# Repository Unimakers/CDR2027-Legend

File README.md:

# CDR 2027 - Legend

Dépôt de l'équipe **Unimakers** (MakerSpace Amiens) pour la **Coupe de France de Robotique 2027**, thème « The Legend of Camelot ».

Nous préparons un **robot principal** et des **PAMI** (petits robots autonomes qui partent de l'écurie en fin de match).

- **Documentation : [unimakers.fr/CDR2027-Legend](https://unimakers.fr/CDR2027-Legend/)** (objectifs, robots, journaux de bord)
- **CAO : [projet Onshape](https://cad.onshape.com/documents/a1dd7e986cf35e5710cc0af1/v/c28c25944dc0cfd69f9db5c7/e/192be7f926e66b5b2fba6ecb)**

## Contenu du dépôt

| Dossier | Contenu |
|:--|:--|
| [`fw/`](fw/) | Firmware des PAMI : ESP32-S3 (PlatformIO, Arduino) et coprocesseur Luckfox (Python) |
| [`ecad/`](ecad/) | Cartes électroniques KiCad : PAMI V1 (en service), PAMI V2 (en conception), robot principal |
| [`mcad/`](mcad/) | Exports de pièces (STL) ; la CAO elle-même est sur Onshape |
| [`docs/`](docs/) | Site de documentation (Jekyll, thème Just the Docs), publié sur GitHub Pages |

## Avancement

- **PAMI** : carte V1 câblée et firmware fonctionnel (odométrie, stratégies en JSON, interface web, mise à jour sans fil). Carte V2 routée, pas encore fabriquée.
- **Robot principal** : carte électronique en cours sous KiCad, module encodeur testé, prototype de l'actionneur de levage des murs. Pas encore de code.

Le détail, semaine par semaine, est dans les [journaux de bord](https://unimakers.fr/CDR2027-Legend/journaux/).

## Démarrer

```sh
# Firmware PAMI (carte V1)
cd fw/fw-pami-carte-v1
pio run

# Site de documentation en local
cd docs
bundle install
bundle exec jekyll serve
```

## Contribuer

Les commits suivent le format `[TAG] Message`, avec les tags `[FW]`, `[DOC]`, `[ECAD]` et `[GLOBAL]`.

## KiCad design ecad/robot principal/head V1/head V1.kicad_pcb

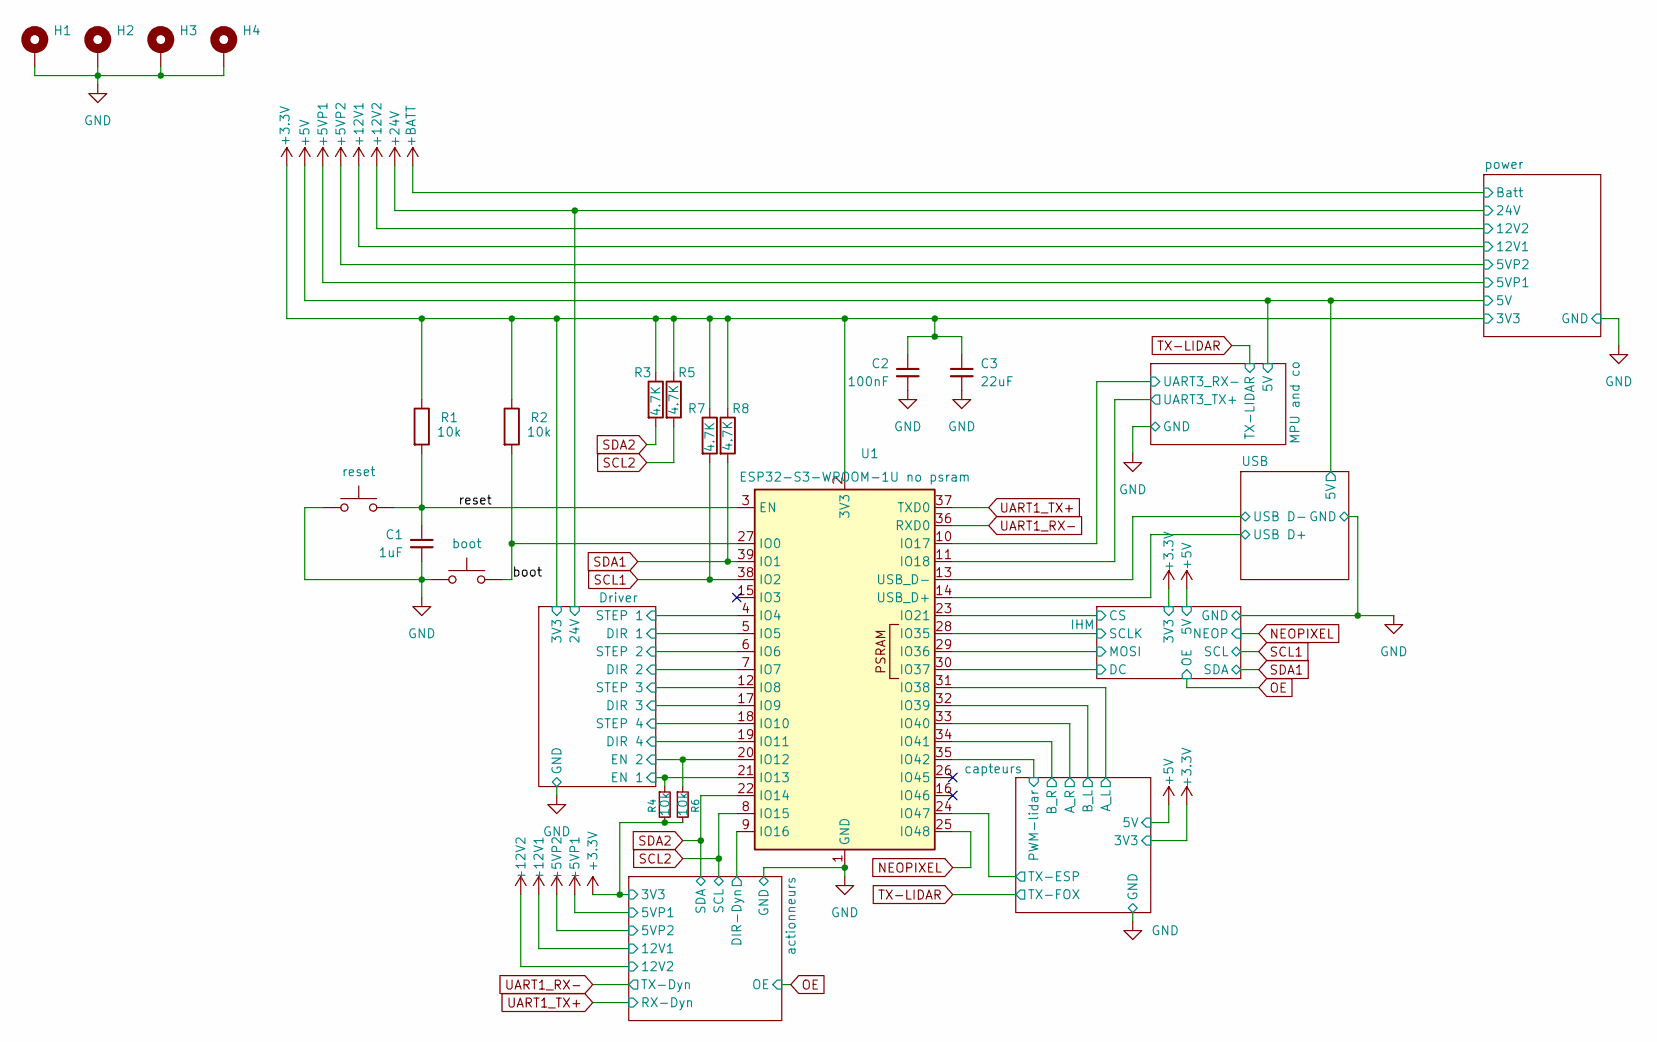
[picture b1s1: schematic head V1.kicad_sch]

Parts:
C1: 1uF; C_0805_2012Metric_Pad1.18x1.45mm_HandSolder
C2: 100nF; C_0805_2012Metric_Pad1.18x1.45mm_HandSolder
C3: 22uF; C_0805_2012Metric_Pad1.18x1.45mm_HandSolder
H1, H2, H3, H4: MountingHole_Pad; MountingHole_3.2mm_M3_Pad_Via
R1, R2, R4, R6: 10k; R_0805_2012Metric_Pad1.20x1.40mm_HandSolder
R3, R5, R7, R8: 4.7K; R_0805_2012Metric_Pad1.20x1.40mm_HandSolder
SW1: reset; SW_Push_SPST_NO_Alps_SKRK
SW2: boot; SW_Push_SPST_NO_Alps_SKRK
U1: ESP32-S3-WROOM-1U no psram; ESP32-S3-WROOM-1U

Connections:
+3.3V: C2.1, C3.1, R1.1, R2.1, R3.1, R4.2, R5.1, R6.2, R7.1, R8.1, U1.2 (3V3); also elsewhere on the board
/Driver/DIR 1: U1.5 (IO5); also elsewhere on the board
/Driver/DIR 2: U1.7 (IO7); also elsewhere on the board
/Driver/DIR 3: U1.17 (IO9); also elsewhere on the board
/Driver/DIR 4: U1.19 (IO11); also elsewhere on the board
/Driver/EN 1: R4.1, U1.21 (IO13); also elsewhere on the board
/Driver/EN 2: R6.1, U1.20 (IO12); also elsewhere on the board
/Driver/STEP 1: U1.4 (IO4); also elsewhere on the board
/Driver/STEP 2: U1.6 (IO6); also elsewhere on the board
/Driver/STEP 3: U1.12 (IO8); also elsewhere on the board
/Driver/STEP 4: U1.18 (IO10); also elsewhere on the board
/IHM/CS: U1.23 (IO21); also elsewhere on the board
/IHM/DC: U1.30 (IO37); also elsewhere on the board
/IHM/MOSI: U1.29 (IO36); also elsewhere on the board
/IHM/SCLK: U1.28 (IO35); also elsewhere on the board
/MPU and co/UART3_RX-: U1.10 (IO17); also elsewhere on the board
/MPU and co/UART3_TX+: U1.11 (IO18); also elsewhere on the board
/USB/USB D+: U1.14 (USB_D+); also elsewhere on the board
/USB/USB D-: U1.13 (USB_D-); also elsewhere on the board
/actionneurs/DIR-Dyn: U1.9 (IO16); also elsewhere on the board
/boot: R2.2, SW2.2, U1.27 (IO0)
/capteurs/A_L: U1.31 (IO38); also elsewhere on the board
/capteurs/A_R: U1.33 (IO40); also elsewhere on the board
/capteurs/B_L: U1.32 (IO39); also elsewhere on the board
/capteurs/B_R: U1.34 (IO41); also elsewhere on the board
/capteurs/PWM-lidar: U1.35 (IO42); also elsewhere on the board
/capteurs/TX-ESP: U1.24 (IO47); also elsewhere on the board
/reset: C1.1, R1.2, SW1.2, U1.3 (EN)
GND: C1.2, C2.2, C3.2, H1.1 (1_1), H2.1 (1_1), H3.1 (1_1), H4.1 (1_1), SW1.1, SW2.1, U1.1 (GND), U1.40 (GND), U1.41 (GND); also elsewhere on the board
NEOPIXEL: U1.25 (IO48); also elsewhere on the board
SCL1: R7.2, U1.38 (IO2); also elsewhere on the board
SCL2: R5.2, U1.8 (IO15); also elsewhere on the board
SDA1: R8.2, U1.39 (IO1); also elsewhere on the board
SDA2: R3.2, U1.22 (IO14); also elsewhere on the board
UART1_RX-: U1.36 (RXD0); also elsewhere on the board
UART1_TX+: U1.37 (TXD0); also elsewhere on the board

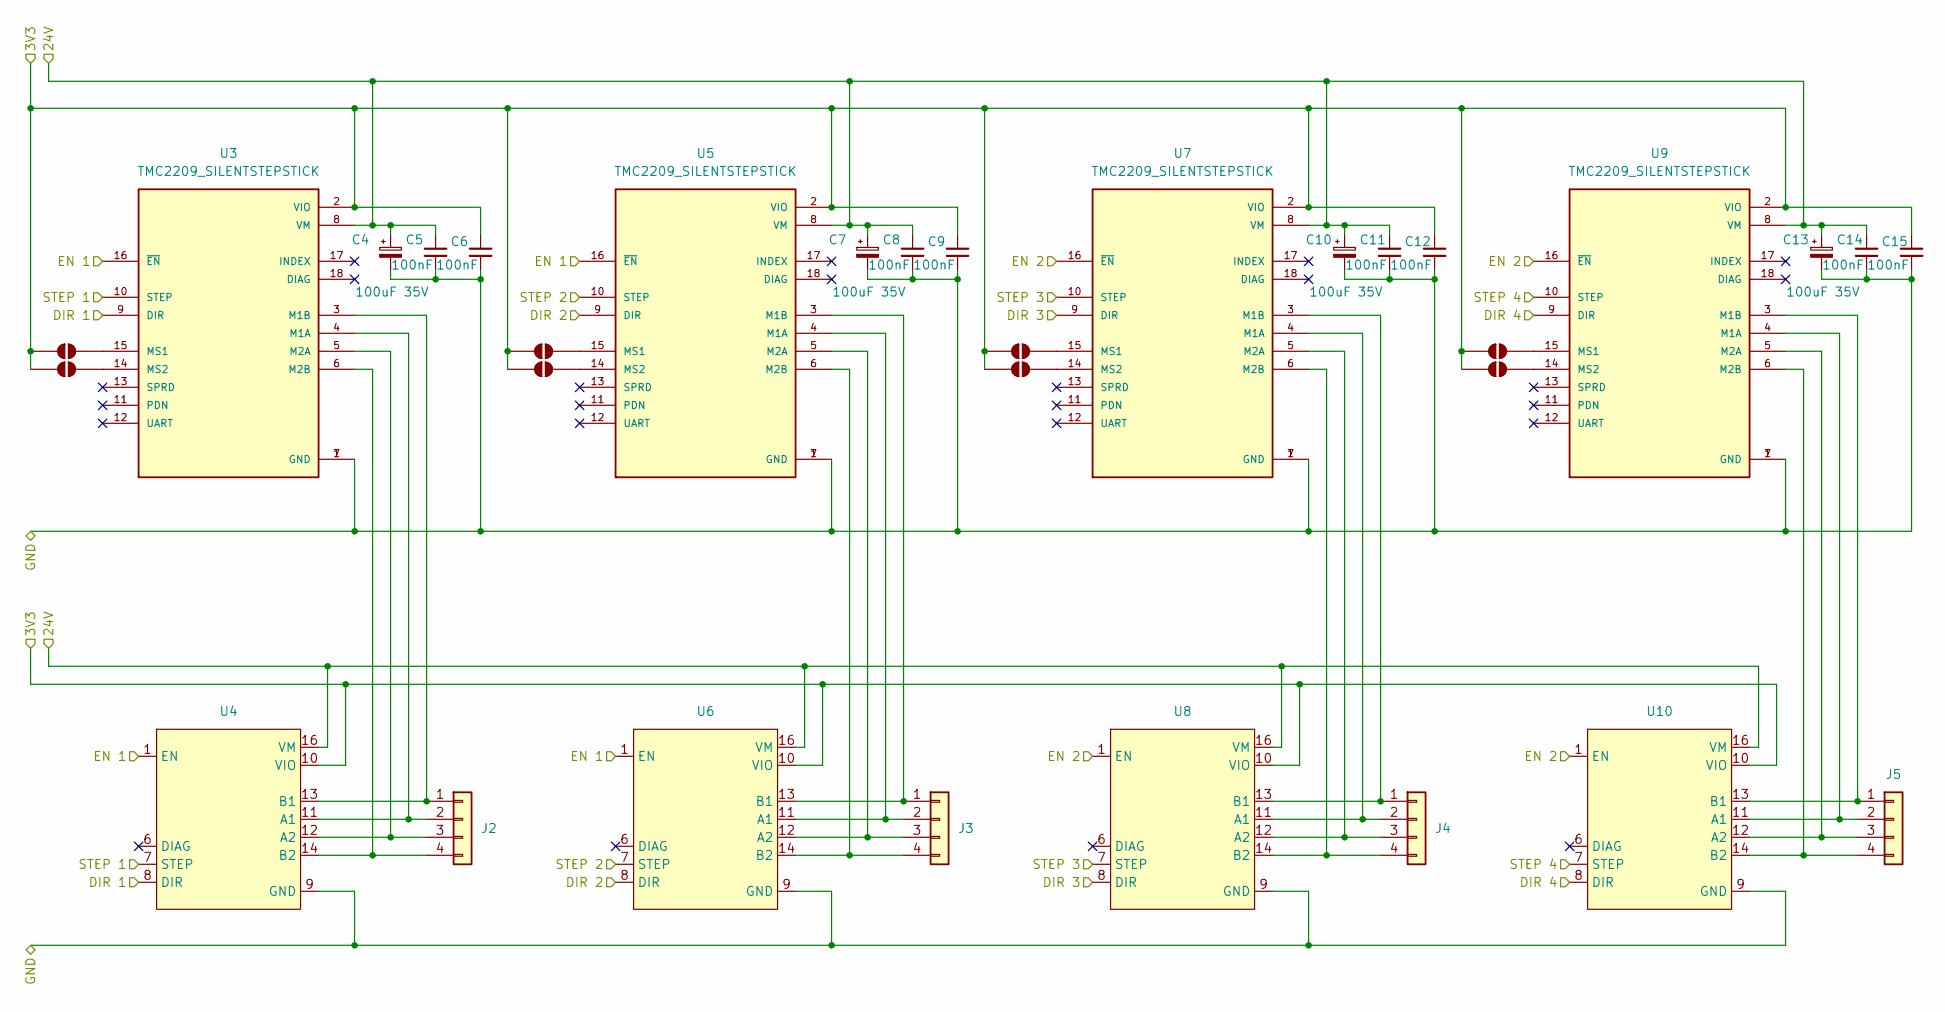
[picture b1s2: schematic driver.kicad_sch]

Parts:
C4, C7, C10, C13: 100uF 35V; CP_Radial_D6.3mm_P2.50mm
C5, C6, C8, C9, C11, C12, C14, C15: 100nF; C_0805_2012Metric_Pad1.18x1.45mm_HandSolder
J2, J3, J4, J5: Conn_01x04; Molex_KK-254_AE-6410-04A_1x04_P2.54mm_Vertical
JP1, JP2, JP3, JP4, JP5, JP6, JP7, JP8: SolderJumper_2_Open; SolderJumper-2_P1.3mm_Open_RoundedPad1.0x1.5mm
U3, U5, U7, U9: TMC2209_SILENTSTEPSTICK; MODULE_TMC2209_SILENTSTEPSTICK; PARTREV 1.20
U4, U6, U8, U10: ez 2209

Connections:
+3.3V: C6.1, C9.1, C12.1, C15.1, JP1.1 (A), JP2.1 (A), JP3.1 (A), JP4.1 (A), JP5.1 (A), JP6.1 (A), JP7.1 (A), JP8.1 (A), U3.2 (VIO), U4.10 (VIO), U5.2 (VIO), U6.10 (VIO), U7.2 (VIO), U8.10 (VIO), U9.2 (VIO), U10.10 (VIO); also elsewhere on the board
+24V: C4.1, C5.1, C7.1, C8.1, C10.1, C11.1, C13.1, C14.1, U3.8 (VM), U4.16 (VM), U5.8 (VM), U6.16 (VM), U7.8 (VM), U8.16 (VM), U9.8 (VM), U10.16 (VM); also elsewhere on the board
/Driver/DIR 1: U3.9 (DIR), U4.8 (DIR); also elsewhere on the board
/Driver/DIR 2: U5.9 (DIR), U6.8 (DIR); also elsewhere on the board
/Driver/DIR 3: U7.9 (DIR), U8.8 (DIR); also elsewhere on the board
/Driver/DIR 4: U9.9 (DIR), U10.8 (DIR); also elsewhere on the board
/Driver/EN 1: U3.16 (~EN), U4.1 (EN), U5.16 (~EN), U6.1 (EN); also elsewhere on the board
/Driver/EN 2: U7.16 (~EN), U8.1 (EN), U9.16 (~EN), U10.1 (EN); also elsewhere on the board
/Driver/STEP 1: U3.10 (STEP), U4.7 (STEP); also elsewhere on the board
/Driver/STEP 2: U5.10 (STEP), U6.7 (STEP); also elsewhere on the board
/Driver/STEP 3: U7.10 (STEP), U8.7 (STEP); also elsewhere on the board
/Driver/STEP 4: U9.10 (STEP), U10.7 (STEP); also elsewhere on the board
GND: C4.2, C5.2, C6.2, C7.2, C8.2, C9.2, C10.2, C11.2, C12.2, C13.2, C14.2, C15.2, U3.1 (GND), U3.7 (GND), U4.9 (GND), U4.15 (GND), U5.1 (GND), U5.7 (GND), U6.9 (GND), U6.15 (GND), U7.1 (GND), U7.7 (GND), U8.9 (GND), U8.15 (GND), U9.1 (GND), U9.7 (GND), U10.9 (GND), U10.15 (GND); also elsewhere on the board
unnamed: J2.1, U3.3 (M1B), U4.13 (B1)
unnamed: J2.2, U3.4 (M1A), U4.11 (A1)
unnamed: J2.3, U3.5 (M2A), U4.12 (A2)
unnamed: J2.4, U3.6 (M2B), U4.14 (B2)
unnamed: J3.1, U5.3 (M1B), U6.13 (B1)
unnamed: J3.2, U5.4 (M1A), U6.11 (A1)
unnamed: J3.3, U5.5 (M2A), U6.12 (A2)
unnamed: J3.4, U5.6 (M2B), U6.14 (B2)
unnamed: J4.1, U7.3 (M1B), U8.13 (B1)
unnamed: J4.2, U7.4 (M1A), U8.11 (A1)
unnamed: J4.3, U7.5 (M2A), U8.12 (A2)
unnamed: J4.4, U7.6 (M2B), U8.14 (B2)
unnamed: J5.1, U9.3 (M1B), U10.13 (B1)
unnamed: J5.2, U9.4 (M1A), U10.11 (A1)
unnamed: J5.3, U9.5 (M2A), U10.12 (A2)
unnamed: J5.4, U9.6 (M2B), U10.14 (B2)
unnamed: JP1.2 (B), U3.15 (MS1)
unnamed: JP2.2 (B), U3.14 (MS2)
unnamed: JP3.2 (B), U5.15 (MS1)
unnamed: JP4.2 (B), U5.14 (MS2)
unnamed: JP5.2 (B), U7.15 (MS1)
unnamed: JP6.2 (B), U7.14 (MS2)
unnamed: JP7.2 (B), U9.15 (MS1)
unnamed: JP8.2 (B), U9.14 (MS2)

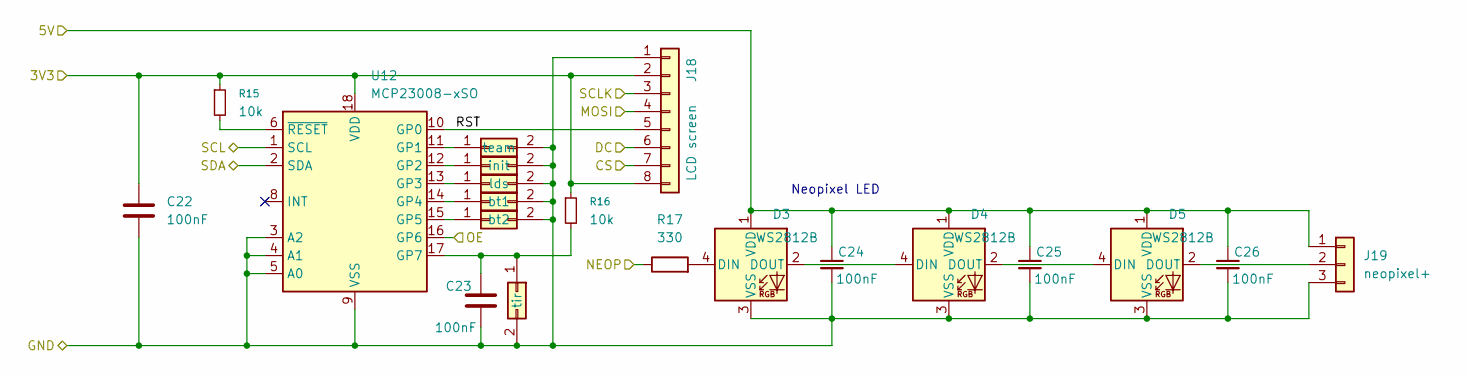
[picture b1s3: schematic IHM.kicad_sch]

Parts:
C22, C23, C24, C25, C26: 100nF; C_0805_2012Metric_Pad1.18x1.45mm_HandSolder
D3, D4, D5: WS2812B; LED_WS2812B_PLCC4_5.0x5.0mm_P3.2mm
J12: team; Molex_KK-254_AE-6410-02A_1x02_P2.54mm_Vertical
J13: init; Molex_KK-254_AE-6410-02A_1x02_P2.54mm_Vertical
J14: lds; Molex_KK-254_AE-6410-02A_1x02_P2.54mm_Vertical
J15: bt1; Molex_KK-254_AE-6410-02A_1x02_P2.54mm_Vertical
J16: bt2; Molex_KK-254_AE-6410-02A_1x02_P2.54mm_Vertical
J17: tir; Molex_KK-254_AE-6410-02A_1x02_P2.54mm_Vertical
J18: LCD screen; PinSocket_1x08_P2.54mm_Vertical
J19: neopixel+; Molex_KK-254_AE-6410-03A_1x03_P2.54mm_Vertical
R15, R16: 10k; R_0805_2012Metric_Pad1.20x1.40mm_HandSolder
R17: 330; R_0805_2012Metric_Pad1.20x1.40mm_HandSolder
U12: MCP23008-xSO; SOIC-18W_7.5x11.6mm_P1.27mm

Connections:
+3.3V: C22.1, J18.2, J18.8, R15.1, R16.1, U12.18 (VDD); also elsewhere on the board
+5V: C24.1, C25.1, C26.1, D3.1 (VDD), D4.1 (VDD), D5.1 (VDD), J19.1; also elsewhere on the board
/IHM/CS: J18.7; also elsewhere on the board
/IHM/DC: J18.6; also elsewhere on the board
/IHM/MOSI: J18.4; also elsewhere on the board
/IHM/RST: J18.5, U12.10 (GP0)
/IHM/SCLK: J18.3; also elsewhere on the board
GND: C22.2, C23.2, C24.2, C25.2, C26.2, D3.3 (VSS), D4.3 (VSS), D5.3 (VSS), J12.2, J13.2, J14.2, J15.2, J16.2, J17.2, J18.1, J19.3, U12.3 (A2), U12.4 (A1), U12.5 (A0), U12.9 (VSS); also elsewhere on the board
NEOPIXEL: R17.1; also elsewhere on the board
unnamed: D3.4 (DIN), R17.2
unnamed: D3.2 (DOUT), D4.4 (DIN)
unnamed: D4.2 (DOUT), D5.4 (DIN)
unnamed: D5.2 (DOUT), J19.2
unnamed: J12.1, U12.11 (GP1)
unnamed: J13.1, U12.12 (GP2)
unnamed: J14.1, U12.13 (GP3)
unnamed: J15.1, U12.14 (GP4)
unnamed: J16.1, U12.15 (GP5)
unnamed: C23.1, J17.1, R16.2, U12.17 (GP7)
unnamed: R15.2, U12.6 (~RESET)
OE: U12.16 (GP6); also elsewhere on the board
SCL1: U12.1 (SCL); also elsewhere on the board
SDA1: U12.2 (SDA); also elsewhere on the board

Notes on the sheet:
Neopixel LED

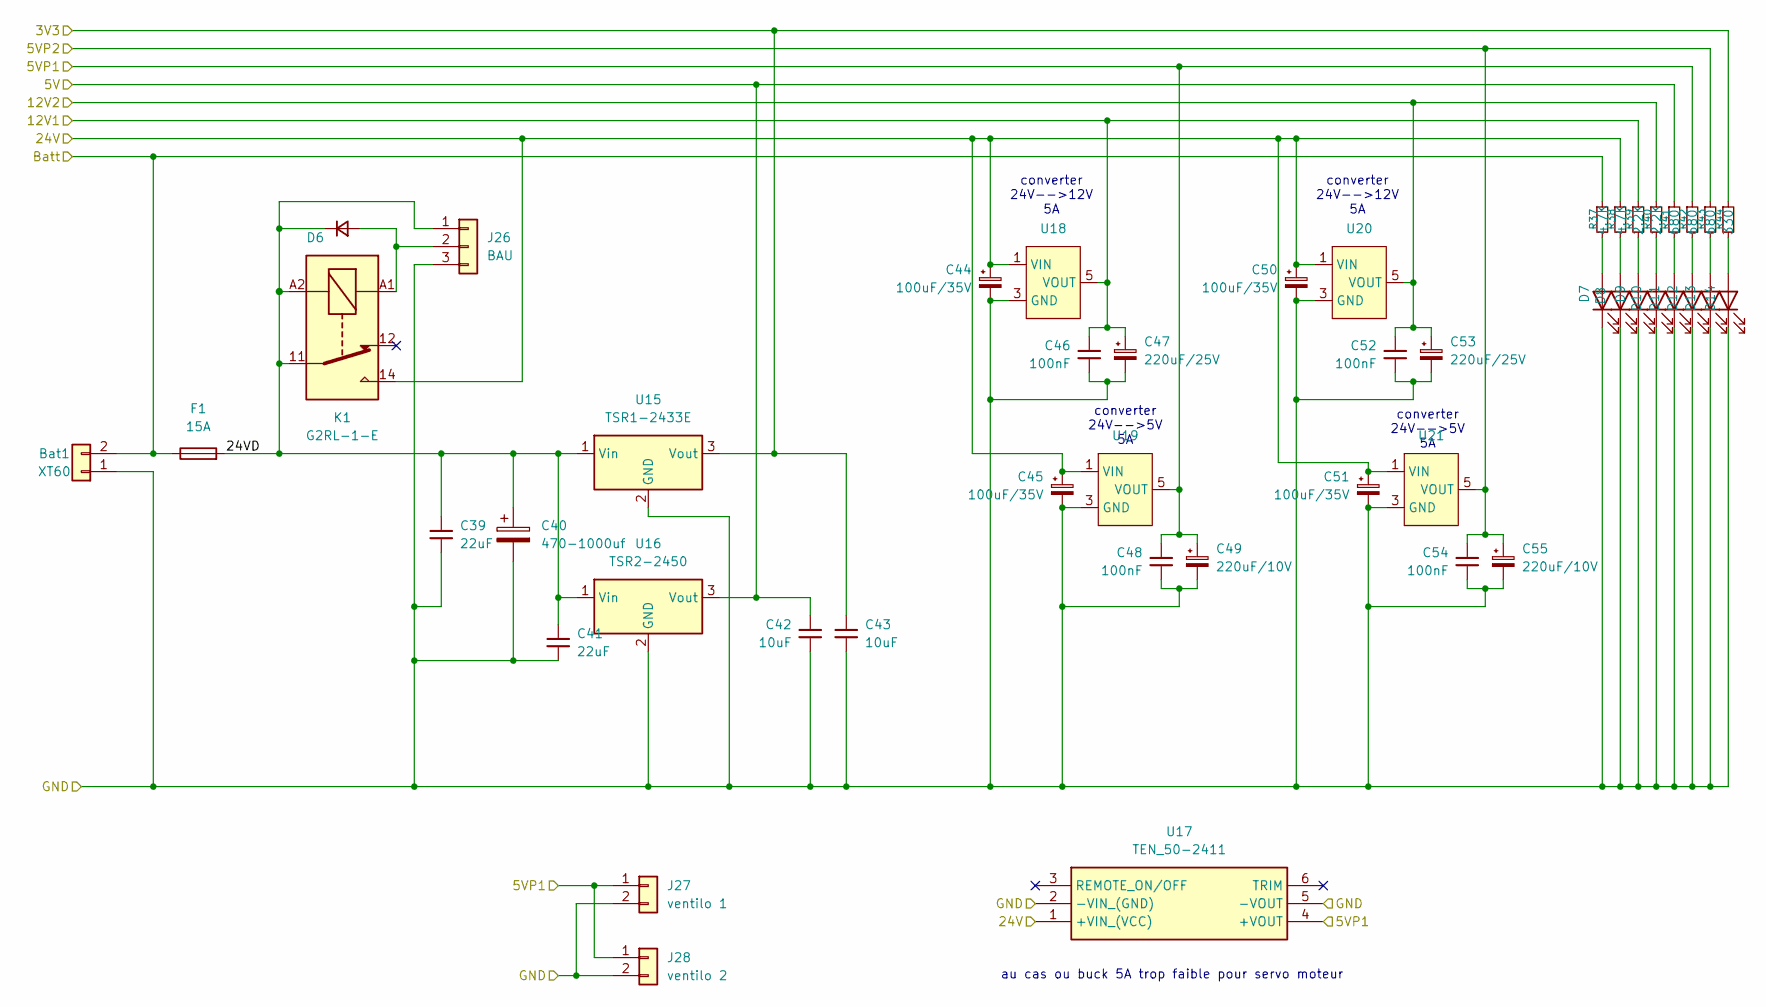
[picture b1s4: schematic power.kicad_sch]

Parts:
Bat1: XT60; AMASS_XT60-M_1x02_P7.20mm_Vertical
C39, C41: 22uF; C_1206_3216Metric_Pad1.33x1.80mm_HandSolder
C40: 470-1000uf; CP_Radial_D10.0mm_P5.00mm
C42, C43: 10uF; C_0805_2012Metric_Pad1.18x1.45mm_HandSolder
C44, C45, C50, C51: 100uF/35V; CP_Radial_D6.3mm_P2.50mm
C46, C48, C52, C54: 100nF; C_0805_2012Metric_Pad1.18x1.45mm_HandSolder
C47, C53: 220uF/25V; CP_Radial_D8.0mm_P3.50mm
C49, C55: 220uF/10V; CP_Radial_D6.3mm_P2.50mm
D6: D_Small; D_SMA_Handsoldering
D7, D8, D9, D10, D11, D12, D13, D14: LED; LED_0805_2012Metric_Pad1.15x1.40mm_HandSolder
F1: 15A; Fuseholder_Blade_Mini_Keystone_3568
J26: BAU; Molex_KK-254_AE-6410-03A_1x03_P2.54mm_Vertical
J27: ventilo 1; Molex_KK-254_AE-6410-02A_1x02_P2.54mm_Vertical
J28: ventilo 2; Molex_KK-254_AE-6410-02A_1x02_P2.54mm_Vertical
K1: G2RL-1-E; Relay_SPDT_Omron_G2RL-1-E
R37, R38: 4.7K; R_0805_2012Metric_Pad1.20x1.40mm_HandSolder
R39, R40: 2.2K; R_0805_2012Metric_Pad1.20x1.40mm_HandSolder
R41, R42, R43: 680; R_0805_2012Metric_Pad1.20x1.40mm_HandSolder
R44: 330; R_0805_2012Metric_Pad1.20x1.40mm_HandSolder
U15: TSR1-2433E; Converter_DCDC_TRACO_TSR1-xxxxE_THT
U16: TSR2-2450; Converter_DCDC_TRACO_TSR2-xxxx_THT
U17: TEN_50-2411; Mouser Part Number 495-TEN-50-2411
U18, U19, U20, U21: Module_Buck_LMR51450_KK254_RightAngle_1x06_P2.54mm

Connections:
+3.3V: C43.1, R44.1, U15.3 (Vout); also elsewhere on the board
+5V: C42.1, R41.1, U16.3 (Vout); also elsewhere on the board
+5VP1: C48.1, C49.1, J27.1, J28.1, R42.1, U17.4 (+VOUT), U19.5 (VOUT), U19.6 (VOUT); also elsewhere on the board
+5VP2: C54.1, C55.1, R43.1, U21.5 (VOUT), U21.6 (VOUT); also elsewhere on the board
+12V1: C46.1, C47.1, R39.1, U18.5 (VOUT), U18.6 (VOUT); also elsewhere on the board
+12V2: C52.1, C53.1, R40.1, U20.5 (VOUT), U20.6 (VOUT); also elsewhere on the board
+24V: C44.1, C45.1, C50.1, C51.1, K1.14, R38.1, U17.1 (+VIN_(VCC)), U18.1 (VIN), U18.2 (VIN), U19.1 (VIN), U19.2 (VIN), U20.1 (VIN), U20.2 (VIN), U21.1 (VIN), U21.2 (VIN); also elsewhere on the board
+BATT: Bat1.2, F1.1, R37.1
/power/24VD: C39.1, C40.1, C41.1, D6.1 (K), F1.2, J26.1, K1.11, K1.A2, U15.1 (Vin), U16.1 (Vin)
GND: Bat1.1, C39.2, C40.2, C41.2, C42.2, C43.2, C44.2, C45.2, C46.2, C47.2, C48.2, C49.2, C50.2, C51.2, C52.2, C53.2, C54.2, C55.2, D7.1 (K), D8.1 (K), D9.1 (K), D10.1 (K), D11.1 (K), D12.1 (K), D13.1 (K), D14.1 (K), J26.3, J27.2, J28.2, U15.2 (GND), U16.2 (GND), U17.2 (-VIN_(GND)), U17.5 (-VOUT), U18.3 (GND), U18.4 (GND), U19.3 (GND), U19.4 (GND), U20.3 (GND), U20.4 (GND), U21.3 (GND), U21.4 (GND); also elsewhere on the board
unnamed: D6.2 (A), J26.2, K1.A1
unnamed: D7.2 (A), R37.2
unnamed: D8.2 (A), R38.2
unnamed: D9.2 (A), R39.2
unnamed: D10.2 (A), R40.2
unnamed: D11.2 (A), R41.2
unnamed: D12.2 (A), R42.2
unnamed: D13.2 (A), R43.2
unnamed: D14.2 (A), R44.2

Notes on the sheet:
converter 24V-->12V 5A
converter 24V-->5V 5A
au cas ou buck 5A trop faible pour servo moteur

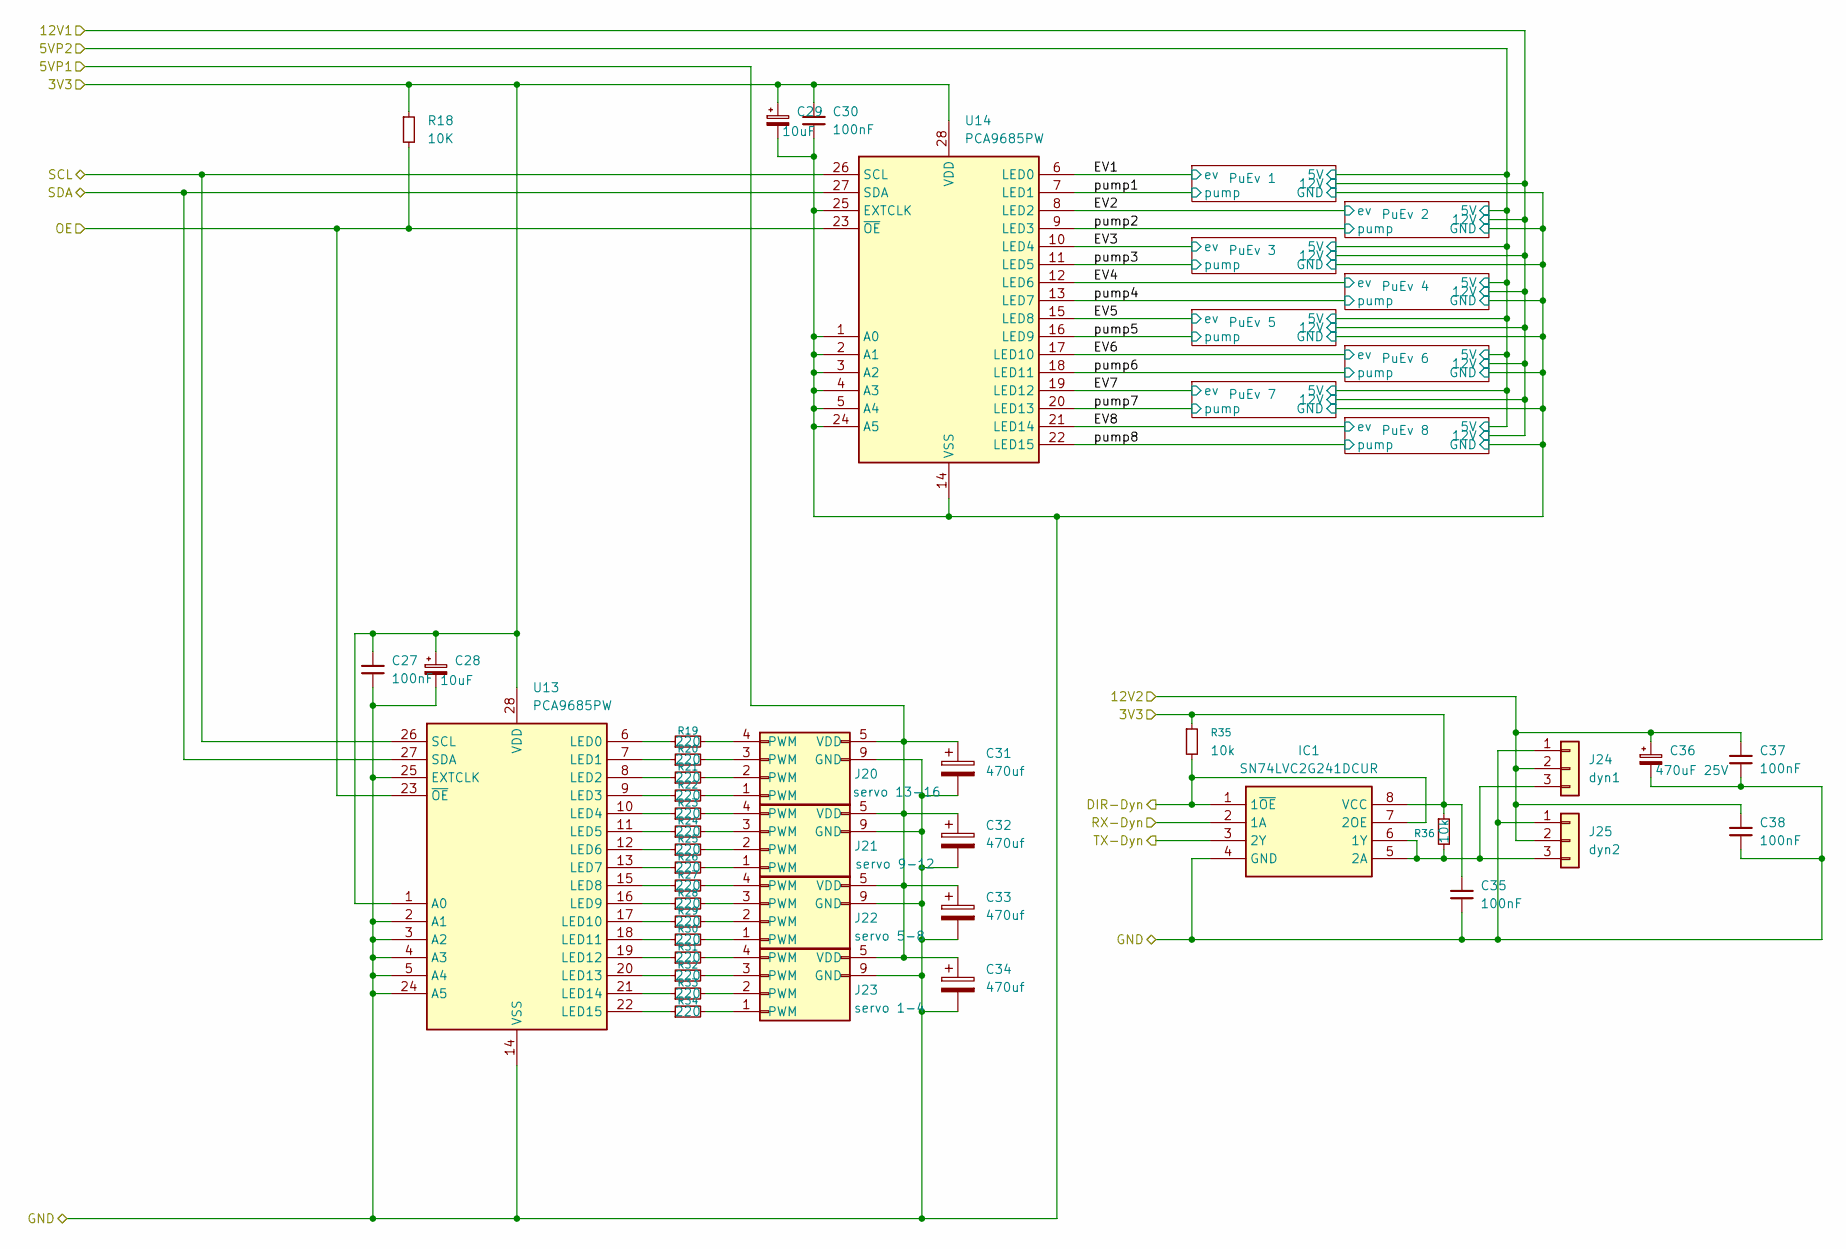
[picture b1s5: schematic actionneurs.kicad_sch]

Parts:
C27, C30, C35, C37, C38: 100nF; C_0805_2012Metric_Pad1.18x1.45mm_HandSolder
C28, C29: 10uF; CP_Radial_D5.0mm_P2.00mm
C31, C32, C33, C34: 470uf; CP_Radial_D8.0mm_P3.50mm
C36: 470uF 25V; CP_Radial_D8.0mm_P3.80mm
IC1: SN74LVC2G241DCUR; SOP50P310X90-8N; Mouser Part Number 595-SN74LVC2G241DCUR
J20: servo 13-16; servo
J21: servo 9-12; servo
J22: servo 5-8; servo
J23: servo 1-4; servo
J24: dyn1; Molex_SPOX_5267-03A_1x03_P2.50mm_Vertical
J25: dyn2; Molex_SPOX_5267-03A_1x03_P2.50mm_Vertical
R18: 10K; R_0805_2012Metric_Pad1.20x1.40mm_HandSolder
R19, R20, R21, R22, R23, R24, R25, R26, R27, R28, R29, R30, R31, R32, R33, R34: 220; R_0805_2012Metric_Pad1.20x1.40mm_HandSolder
R35, R36: 10k; R_0805_2012Metric_Pad1.20x1.40mm_HandSolder
U13, U14: PCA9685PW; TSSOP-28_4.4x9.7mm_P0.65mm

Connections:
+3.3V: C27.1, C28.1, C29.1, C30.1, C35.1, IC1.8 (VCC), R18.1, R35.1, R36.1, U13.1 (A0), U13.28 (VDD), U14.28 (VDD); also elsewhere on the board
+5VP1: C31.1, C32.1, C33.1, C34.1, J20.5 (VDD), J20.6 (VDD), J20.7 (VDD), J20.8 (VDD), J21.5 (VDD), J21.6 (VDD), J21.7 (VDD), J21.8 (VDD), J22.5 (VDD), J22.6 (VDD), J22.7 (VDD), J22.8 (VDD), J23.5 (VDD), J23.6 (VDD), J23.7 (VDD), J23.8 (VDD); also elsewhere on the board
+12V2: C36.1, C37.1, C38.1, J24.2, J25.2; also elsewhere on the board
/actionneurs/DIR-Dyn: IC1.1 (1~OE), IC1.7 (2OE), R35.2; also elsewhere on the board
/actionneurs/EV1: U14.6 (LED0); also elsewhere on the board
/actionneurs/EV2: U14.8 (LED2); also elsewhere on the board
/actionneurs/EV3: U14.10 (LED4); also elsewhere on the board
/actionneurs/EV4: U14.12 (LED6); also elsewhere on the board
/actionneurs/EV5: U14.15 (LED8); also elsewhere on the board
/actionneurs/EV6: U14.17 (LED10); also elsewhere on the board
/actionneurs/EV7: U14.19 (LED12); also elsewhere on the board
/actionneurs/EV8: U14.21 (LED14); also elsewhere on the board
/actionneurs/pump1: U14.7 (LED1); also elsewhere on the board
/actionneurs/pump2: U14.9 (LED3); also elsewhere on the board
/actionneurs/pump3: U14.11 (LED5); also elsewhere on the board
/actionneurs/pump4: U14.13 (LED7); also elsewhere on the board
/actionneurs/pump5: U14.16 (LED9); also elsewhere on the board
/actionneurs/pump6: U14.18 (LED11); also elsewhere on the board
/actionneurs/pump7: U14.20 (LED13); also elsewhere on the board
/actionneurs/pump8: U14.22 (LED15); also elsewhere on the board
GND: C27.2, C28.2, C29.2, C30.2, C31.2, C32.2, C33.2, C34.2, C35.2, C36.2, C37.2, C38.2, IC1.4 (GND), J20.9 (GND), J20.10 (GND), J20.11 (GND), J20.12 (GND), J21.9 (GND), J21.10 (GND), J21.11 (GND), J21.12 (GND), J22.9 (GND), J22.10 (GND), J22.11 (GND), J22.12 (GND), J23.9 (GND), J23.10 (GND), J23.11 (GND), J23.12 (GND), J24.1, J25.1, U13.2 (A1), U13.3 (A2), U13.4 (A3), U13.5 (A4), U13.14 (VSS), U13.24 (A5), U13.25 (EXTCLK), U14.1 (A0), U14.2 (A1), U14.3 (A2), U14.4 (A3), U14.5 (A4), U14.14 (VSS), U14.24 (A5), U14.25 (EXTCLK); also elsewhere on the board
unnamed: IC1.5 (2A), IC1.6 (1Y), J24.3, J25.3, R36.2
unnamed: J20.1 (PWM), R22.2
unnamed: J20.2 (PWM), R21.2
unnamed: J20.3 (PWM), R20.2
unnamed: J20.4 (PWM), R19.2
unnamed: J21.1 (PWM), R26.2
unnamed: J21.2 (PWM), R25.2
unnamed: J21.3 (PWM), R24.2
unnamed: J21.4 (PWM), R23.2
unnamed: J22.1 (PWM), R30.2
unnamed: J22.2 (PWM), R29.2
unnamed: J22.3 (PWM), R28.2
unnamed: J22.4 (PWM), R27.2
unnamed: J23.1 (PWM), R34.2
unnamed: J23.2 (PWM), R33.2
unnamed: J23.3 (PWM), R32.2
unnamed: J23.4 (PWM), R31.2
unnamed: R19.1, U13.6 (LED0)
unnamed: R20.1, U13.7 (LED1)
unnamed: R21.1, U13.8 (LED2)
unnamed: R22.1, U13.9 (LED3)
unnamed: R23.1, U13.10 (LED4)
unnamed: R24.1, U13.11 (LED5)
unnamed: R25.1, U13.12 (LED6)
unnamed: R26.1, U13.13 (LED7)
unnamed: R27.1, U13.15 (LED8)
unnamed: R28.1, U13.16 (LED9)
unnamed: R29.1, U13.17 (LED10)
unnamed: R30.1, U13.18 (LED11)
unnamed: R31.1, U13.19 (LED12)
unnamed: R32.1, U13.20 (LED13)
unnamed: R33.1, U13.21 (LED14)
unnamed: R34.1, U13.22 (LED15)
OE: R18.2, U13.23 (~OE), U14.23 (~OE); also elsewhere on the board
SCL2: U13.26 (SCL), U14.26 (SCL); also elsewhere on the board
SDA2: U13.27 (SDA), U14.27 (SDA); also elsewhere on the board
UART1_RX-: IC1.3 (2Y); also elsewhere on the board
UART1_TX+: IC1.2 (1A); also elsewhere on the board

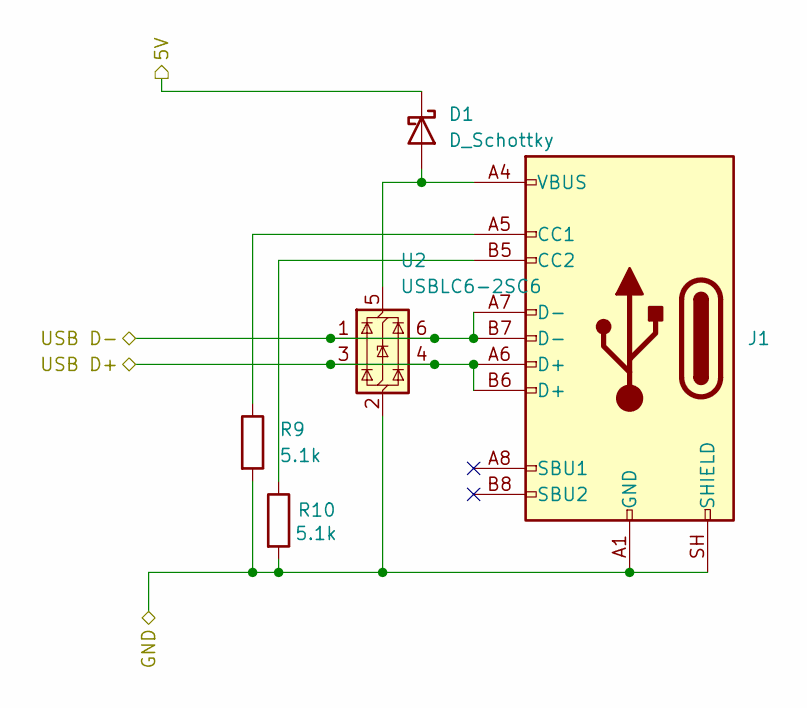
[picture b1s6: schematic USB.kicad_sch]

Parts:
D1: D_Schottky; D_0805_2012Metric_Pad1.15x1.40mm_HandSolder
J1: USB_C_Receptacle_USB2.0_16P; USB_C_Receptacle_HRO_TYPE-C-31-M-12
R9, R10: 5.1k; R_0805_2012Metric_Pad1.20x1.40mm_HandSolder
U2: USBLC6-2SC6; SOT-23-6

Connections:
/USB/USB D+: J1.A6 (D+), J1.B6 (D+), U2.3 (I/O2), U2.4 (I/O2); also elsewhere on the board
/USB/USB D-: J1.A7 (D-), J1.B7 (D-), U2.1 (I/O1), U2.6 (I/O1); also elsewhere on the board
GND: J1.A1 (GND), J1.A12 (GND), J1.B1 (GND), J1.B12 (GND), J1.SH (SHIELD), R9.2, R10.2, U2.2 (GND); also elsewhere on the board
unnamed: J1.A5 (CC1), R9.1
unnamed: J1.B5 (CC2), R10.1
unnamed: D1.2 (A), J1.A4 (VBUS), J1.A9 (VBUS), J1.B4 (VBUS), J1.B9 (VBUS), U2.5 (VBUS)

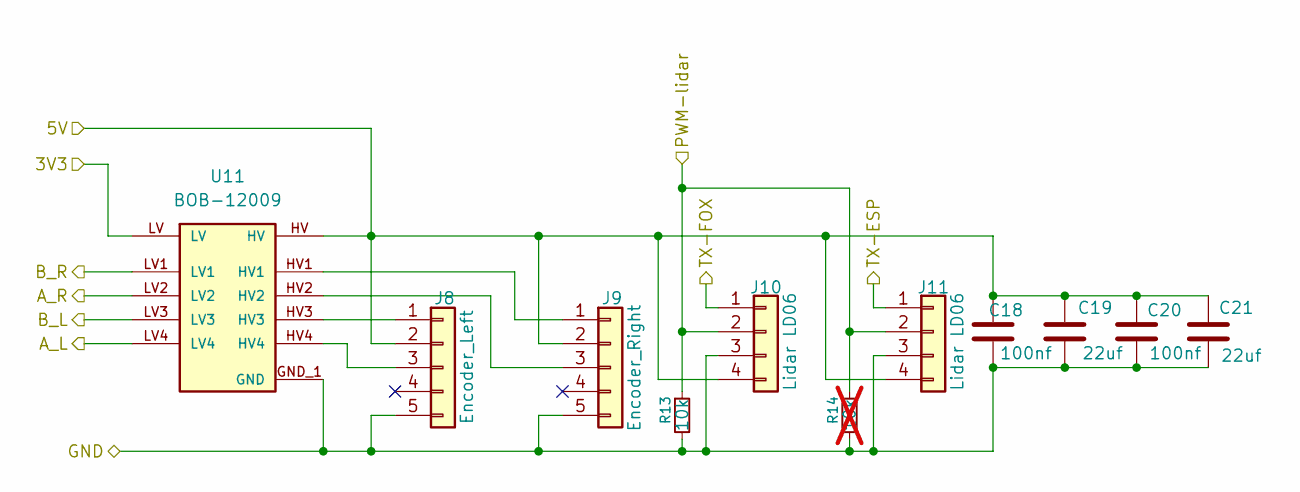
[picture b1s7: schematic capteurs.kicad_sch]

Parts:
C18, C20: 100nf; C_0805_2012Metric_Pad1.18x1.45mm_HandSolder
C19, C21: 22uf; C_0805_2012Metric_Pad1.18x1.45mm_HandSolder
J8: Encoder_Left; Molex_KK-254_AE-6410-05A_1x05_P2.54mm_Vertical
J9: Encoder_Right; Molex_KK-254_AE-6410-05A_1x05_P2.54mm_Vertical
J10, J11: Lidar LD06; Molex_KK-254_AE-6410-04A_1x04_P2.54mm_Vertical
R13: 10k; R_0805_2012Metric_Pad1.20x1.40mm_HandSolder
R14: 10k; R_0805_2012Metric_Pad1.20x1.40mm_HandSolder; not fitted
U11: BOB-12009; CONV_BOB-12009; PARTREV 01

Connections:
+3.3V: U11.LV; also elsewhere on the board
+5V: C18.1, C19.1, C20.1, C21.1, J8.2, J9.2, J10.4, J11.4, U11.HV; also elsewhere on the board
/capteurs/A_L: U11.LV4; also elsewhere on the board
/capteurs/A_R: U11.LV2; also elsewhere on the board
/capteurs/B_L: U11.LV3; also elsewhere on the board
/capteurs/B_R: U11.LV1; also elsewhere on the board
/capteurs/PWM-lidar: J10.2, J11.2, R13.1, R14.1; also elsewhere on the board
/capteurs/TX-ESP: J11.1; also elsewhere on the board
GND: C18.2, C19.2, C20.2, C21.2, J8.5, J9.5, J10.3, J11.3, R13.2, R14.2, U11.GND_1 (GND), U11.GND_2 (GND); also elsewhere on the board
unnamed: J8.1, U11.HV3
unnamed: J8.3, U11.HV4
unnamed: J9.1, U11.HV1
unnamed: J9.3, U11.HV2
TX-LIDAR: J10.1; also elsewhere on the board

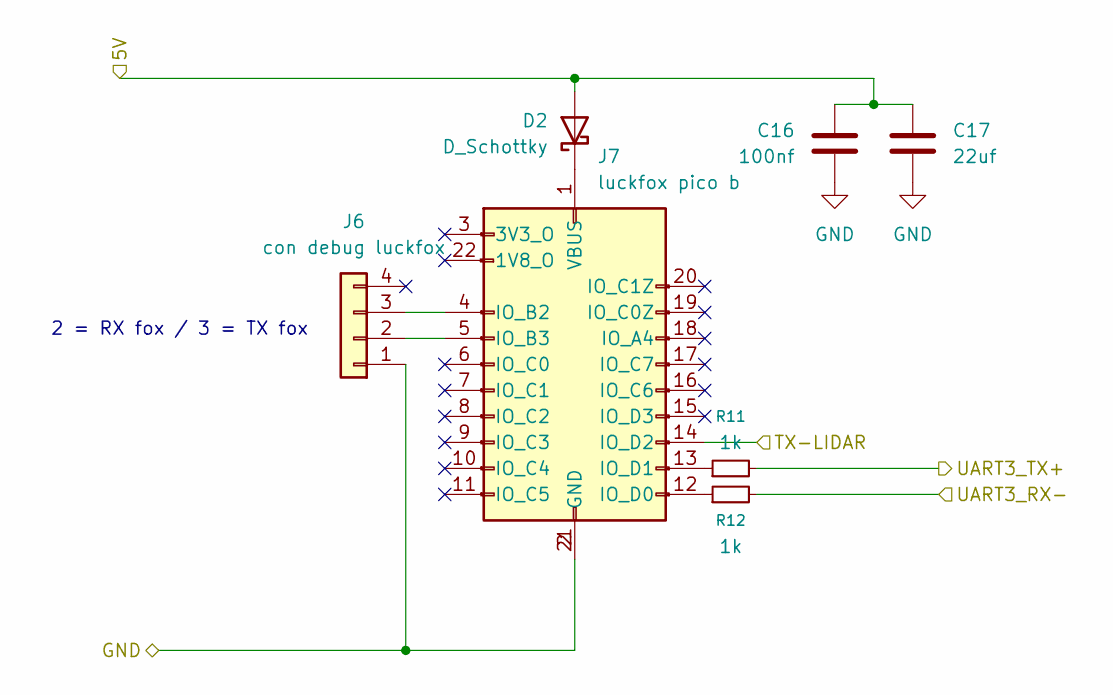
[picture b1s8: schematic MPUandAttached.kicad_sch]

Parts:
C16: 100nf; C_0805_2012Metric_Pad1.18x1.45mm_HandSolder
C17: 22uf; C_0805_2012Metric_Pad1.18x1.45mm_HandSolder
D2: D_Schottky; D_0805_2012Metric_Pad1.15x1.40mm_HandSolder
J6: con debug luckfox; PinHeader_1x04_P2.54mm_Vertical
J7: luckfox pico b; Luckfox_Pico_Mini_THT_2x11_P2.54mm_Row17.78mm
R11, R12: 1k; R_0805_2012Metric_Pad1.20x1.40mm_HandSolder

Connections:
+5V: C16.1, C17.1, D2.2 (A); also elsewhere on the board
/MPU and co/UART3_RX-: R12.2; also elsewhere on the board
/MPU and co/UART3_TX+: R11.2; also elsewhere on the board
GND: C16.2, C17.2, J6.1, J7.2 (GND), J7.21 (GND); also elsewhere on the board
unnamed: D2.1 (K), J7.1 (VBUS)
unnamed: J6.2, J7.5 (IO_B3)
unnamed: J6.3, J7.4 (IO_B2)
unnamed: J7.12 (IO_D0), R12.1
unnamed: J7.13 (IO_D1), R11.1
TX-LIDAR: J7.14 (IO_D2); also elsewhere on the board

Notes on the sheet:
2 = RX fox / 3 = TX fox
